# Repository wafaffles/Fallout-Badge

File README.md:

# Fallout-Badge

My badge for fallout, its great

This is my badge for use at Fallout! Its silly and goofy like me. It has a chaotic LED circuit based on (this)[https://www.creative-science.org.uk/chaotic_leds.html] one. I wanted something fun so it plugs into your PC then does something cool. It just blinks randomly based on some 555 timers being connected together.

##BOM

| Designator                                        | Footprint                | Quantity | Value     | LCSC Part # |
|---------------------------------------------------|--------------------------|----------|-----------|-------------|
| C1, C10, C12, C3, C4, C6, C7, C9                  | 0603                     | 8        | 10u       |             |
| C11, C2, C5, C8                                   | 0603                     | 4        | 0.1u      |             |
| D1, D10, D11, D12, D2, D3, D4, D5, D6, D7, D8, D9 | 0805                     | 12       | LED_Small |             |
| J1                                                | PCB_USB_A                | 1        | USB_A     |             |
| R1, R4, R6, R8                                    | 0603                     | 4        | 100k      |             |
| R10, R11, R12, R13, R14, R9                       | 0603                     | 6        | 680       |             |
| R2, R3, R5, R7                                    | 0603                     | 4        | 220       |             |
| U1, U2, U3, U4                                    | SOIC-8_3.9x4.9mm_P1.27mm | 4        | NE555D    |             |

##Pics

find me on slack at @wafaffles

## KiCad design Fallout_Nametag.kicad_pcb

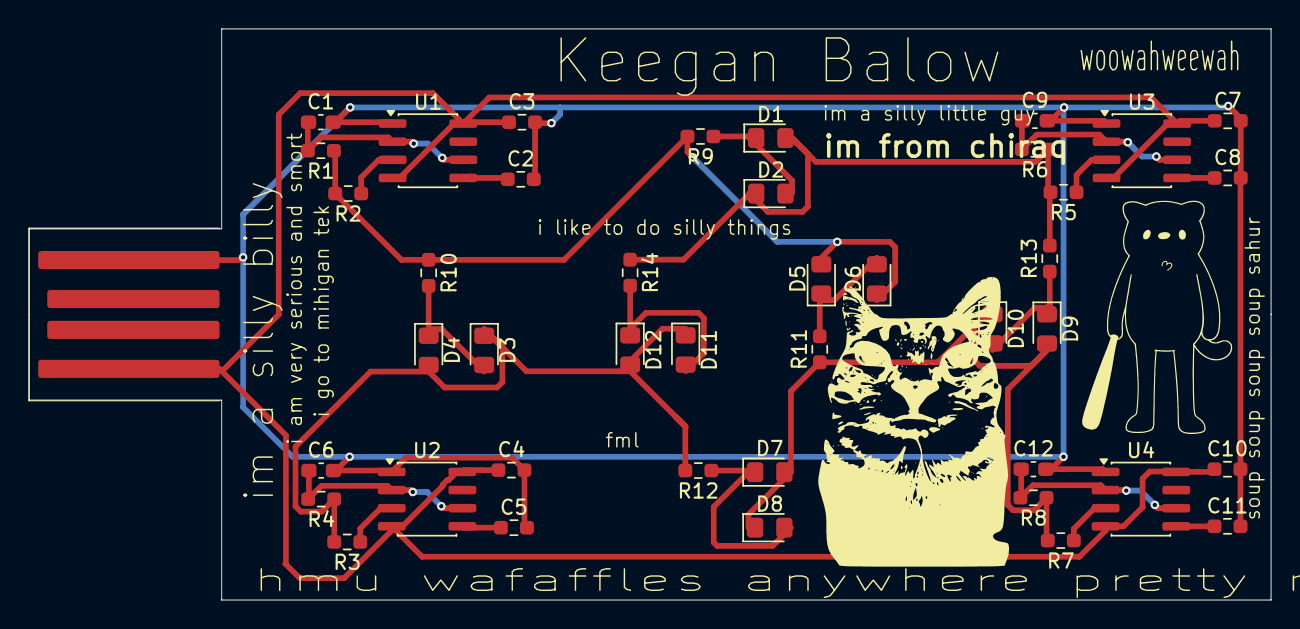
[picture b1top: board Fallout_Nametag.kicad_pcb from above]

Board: 2 copper layers, 87.0 x 40.0 mm, 60 parts (15 on the bottom side), 24 nets.

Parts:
C1, C6, C9, C12: 10u; C_0603_1608Metric_Pad1.08x0.95mm_HandSolder
C2, C5, C8, C11: 0.1u; R_0603_1608Metric_Pad0.98x0.95mm_HandSolder
C3, C4, C7, C10: 10u; R_0603_1608Metric_Pad0.98x0.95mm_HandSolder
D1, D2, D3, D4, D5, D6, D7, D8, D9, D10, D11, D12: LED_Small; LED_0805_2012Metric_Pad1.15x1.40mm_HandSolder
G1, G2, G3, G4, G5, G6, G7, G8, G9, G10, G11, G12, G13, G14, G15, G16, G17: LOGO
J1: USB_A; PCB_USB_A
R1, R4, R6, R8: 100k; R_0603_1608Metric_Pad0.98x0.95mm_HandSolder
R2, R3, R5, R7: 220; R_0603_1608Metric_Pad0.98x0.95mm_HandSolder
R9, R10, R11, R12, R13, R14: 680; R_0603_1608Metric_Pad0.98x0.95mm_HandSolder
U1, U2, U3, U4: NE555D; SOIC-8_3.9x4.9mm_P1.27mm

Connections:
/Timer Circuit1/TO_LEDS: D3.1 (K), D4.2 (A), D11.1 (K), D12.2 (A), R3.2, R4.1, R12.2
/Timer Circuit2/TO_LEDS: D1.2 (A), D2.1 (K), R5.2, R6.1, R13.2, R14.1
/Timer Circuit3/TO_LEDS: D7.2 (A), D8.1 (K), D9.2 (A), D10.1 (K), R7.2, R8.1, R11.1
/Timer Circuit/0V: C1.2, C2.2, C3.2, C4.2, C5.2, C6.2, C7.2, C8.2, C9.2, C10.2, C11.2, C12.2, J1.4 (GND), U1.1 (GND), U2.1 (GND), U3.1 (GND), U4.1 (GND)
/Timer Circuit/+5V: C3.1, C4.1, C7.1, C10.1, J1.1 (VBUS), U1.4 (~RST), U1.8 (VCC), U2.4 (~RST), U2.8 (VCC), U3.4 (~RST), U3.8 (VCC), U4.4 (~RST), U4.8 (VCC)
/Timer Circuit/TO_LEDS: D5.2 (A), D6.1 (K), R1.1, R2.2, R9.2, R10.1
unnamed: D1.1 (K), D2.2 (A), R9.1
unnamed: D3.2 (A), D4.1 (K), R10.2
unnamed: D5.1 (K), D6.2 (A), R11.2
unnamed: D7.1 (K), D8.2 (A), R12.1
unnamed: D9.1 (K), D10.2 (A), R13.1
unnamed: D11.2 (A), D12.1 (K), R14.2
unnamed: C2.1, U1.5 (CONT)
unnamed: R2.1, U1.3 (OUT)
unnamed: C1.1, R1.2, U1.2 (TRIG), U1.6 (THRES)
unnamed: C5.1, U2.5 (CONT)
unnamed: R3.1, U2.3 (OUT)
unnamed: C6.1, R4.2, U2.2 (TRIG), U2.6 (THRES)
unnamed: C8.1, U3.5 (CONT)
unnamed: R5.1, U3.3 (OUT)
unnamed: C9.1, R6.2, U3.2 (TRIG), U3.6 (THRES)
unnamed: C11.1, U4.5 (CONT)
unnamed: R7.1, U4.3 (OUT)
unnamed: C12.1, R8.2, U4.2 (TRIG), U4.6 (THRES)

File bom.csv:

Designator,Footprint,Quantity,Value,LCSC Part #
"C1, C10, C12, C3, C4, C6, C7, C9",0603,8,10u,
"C11, C2, C5, C8",0603,4,0.1u,
"D1, D10, D11, D12, D2, D3, D4, D5, D6, D7, D8, D9",0805,12,LED_Small,
J1,PCB_USB_A,1,USB_A,
"R1, R4, R6, R8",0603,4,100k,
"R10, R11, R12, R13, R14, R9",0603,6,680,
"R2, R3, R5, R7",0603,4,220,
"U1, U2, U3, U4",SOIC-8_3.9x4.9mm_P1.27mm,4,NE555D,
